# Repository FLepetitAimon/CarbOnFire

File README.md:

# Système CarbOnFire
***
## Contexte 
Le projet a été réalisé entre juin et aout 2021 au laboratoire d'aérologie de Toulouse, dans le cadre d'un stage de 4é année d'école d'ingénieur. La stage a été fait par François LEPETIT-AIMON et tutoré par Jean-François LEON. Si vous désirez des informations suplémentaires sur le projet, n'hésitez à contacter François LEPETIT-AIMON à l'adresse mail: francois.lepetitaimon@gmail.com

## Présentation du projet

ATTENTION : Avant d’utiliser le système, veillez à lire la fiche technique du projet.

CarbOnFire est un système de mesure d’émission de particules issues de la combustion de végétaux. Il s’inscrit dans un projet d’étude de l’exposition humaine aux particules fines issues de la combustion de biomasse et en particulier aux feux de forêt. Il est affilié au projet FIRECASTER de l’Agence National de la Recherche (ANR). Ce projet a pour but la création d'une plate-forme numérique de simulation des incendies de forêts et des panaches de fumée associées en zone méditerranéenne. Pour évaluer la quantité de fumée émise par un incendie, il est nécessaire de connaître les facteurs d'émission des polluants.  Les facteurs d’émission se définissent comme la masse d'un polluant spécifique émis dans l’atmosphère par kilogramme de végétation brûlée. Pour les évaluer, on mesure les rapports d'émission qui se définissent comme le rapport entre la masse de polluants émises sur celle des concentrations de CO et CO2. 

CarbOnFire est un système qui permet d’analyser la composition de fumées issues de combustions de végétaux. Le système est installé sur un sac à dos pour être facilement transportable.  Il est équipé d’un système de pompage qui aspire les fumées. L’aspiration se fait au bout d’un tuyau que l’utilisateur place au-dessus des feux. Le bout du tuyau est pourvu d’un filtre de quartz dont le rôle est de capter les particules. Après la mesure, le filtre est analysé au laboratoire par des méthodes chimiques, qui permettent de mettre en évidence sa composition. Les fumées filtrées qui arrivent du tuyau, circulent respectivement dans la pompe, le boîtier de mesure et enfin à travers le compteur à gaz. Elles sont ensuite rejetées dans l’air. Le cœur du système réside dans le boîtier de mesure. Il fait l’acquisition des concentrations de monoxyde (CO) et dioxyde de carbone (CO2), de la température et de la pression. Il enregistre les mesures dans une carte SD pour un traitement ultérieur, et transmet en direct, via Bluetooth, les mesures de gaz et de température. Celles-ci peuvent être visualisées sur le terrain avec un smartphone grâce à l’application CarbOnFire.

## Etat de fonctionnement du système

A l'issue des trois mois de développement, le premier prototype du système est en état de marche. Il fait l'acquisition des mesures de CO, CO2, température et pression. Il enregistre les données sur une carte SD et transmet les mesure de CO, CO2 et température vers une application android. L'ensemble du système est intégré sur un sac à dos. Les mesures réalisées en laboratoire et en conditions reélles ont permis de caractériser la qualité des mesures de gaz. Il en ressort qu la précision obtenue est insuffisante et qu'il faut l'améliorer. Le détail des mesures et de leur analyse est décrit dans la fiche technique du Projet.

## Contenu du Github

Le github contient les programmes arduino du projet, les documents techniques, le code de l'application android avec le fichier .apk, les fichiers des mesures réalisées, et enfin les fichiers associés à la conception du PCB.

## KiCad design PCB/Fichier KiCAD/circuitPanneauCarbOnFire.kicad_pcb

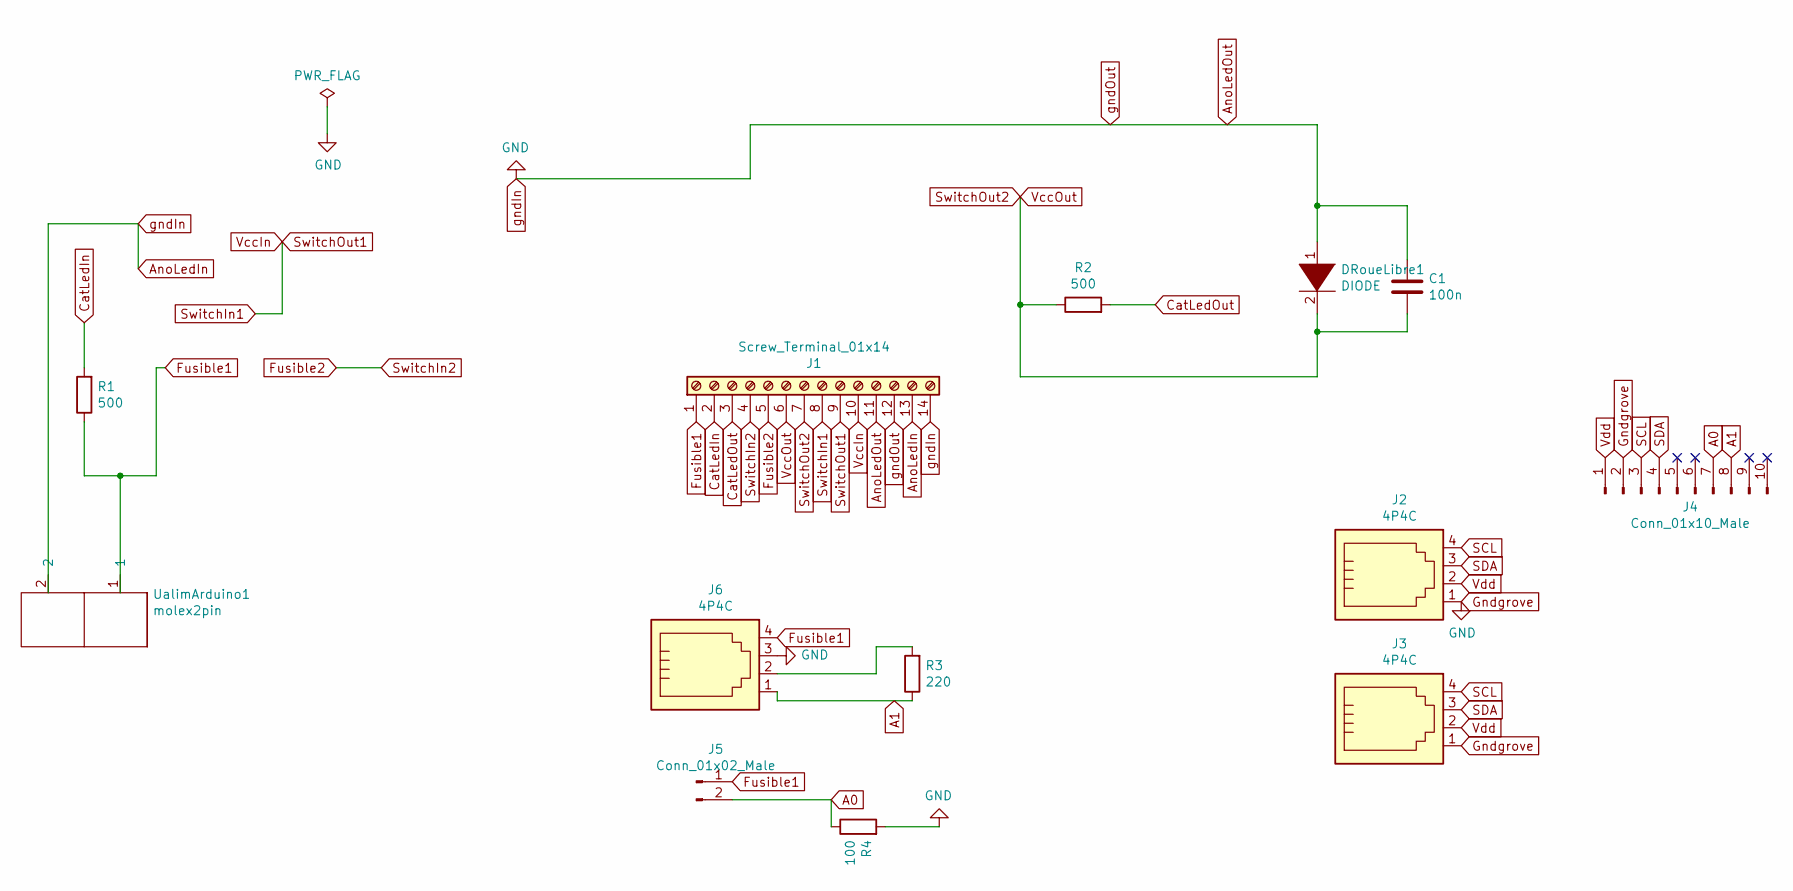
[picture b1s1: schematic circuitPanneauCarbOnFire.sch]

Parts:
C1: 100n; C_Rect_L9.0mm_W2.6mm_P7.50mm_MKT
DRoueLibre1: DIODE; D_A-405_P7.62mm_Horizontal
J1: Screw_Terminal_01x14; TerminalBlock_Phoenix_PT-1,5-14-5.0-H_1x14_P5.00mm_Horizont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
J2, J3: 4P4C; NS-Tech_Grove_1x04_P2mm_Vertical
J4: Conn_01x10_Male; PinSocket_1x10_P2.54mm_Vertical
J5: Conn_01x02_Male; Molex_KK-254_AE-6410-02A_1x02_P2.54mm_Vertical
J6: 4P4C; Molex_SL_171971-0004_1x04_P2.54mm_Vertical
R1, R2: 500; R_Axial_DIN0207_L6.3mm_D2.5mm_P10.16mm_Horizontal
R3: 220; R_Axial_DIN0207_L6.3mm_D2.5mm_P10.16mm_Horizontal
R4: 100; R_Axial_DIN0207_L6.3mm_D2.5mm_P10.16mm_Horizontal
UalimArduino1: molex2pin; Molex_KK-254_AE-6410-02A_1x02_P2.54mm_Vertical

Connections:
A0: J4.7, J5.2, R4.1
A1: J4.8, J6.1, R3.1
AnoLedIn: C1.2, DRoueLibre1.1 (K), J1.11, J1.12, J1.13, J1.14, J2.1, J3.1, J4.2, J6.3, R4.2, UalimArduino1.2
CatLedIn: J1.2, R1.2
CatLedOut: J1.3, R2.2
Fusible1: J1.1, J5.1, J6.4, R1.1, UalimArduino1.1
Fusible2: J1.4, J1.5
unnamed: J6.2, R3.2
SCL: J2.4, J3.4, J4.3
SDA: J2.3, J3.3, J4.4
SwitchIn1: J1.8, J1.9, J1.10
SwitchOut2: C1.1, DRoueLibre1.2 (A), J1.6, J1.7, R2.1
Vdd: J2.2, J3.2, J4.1

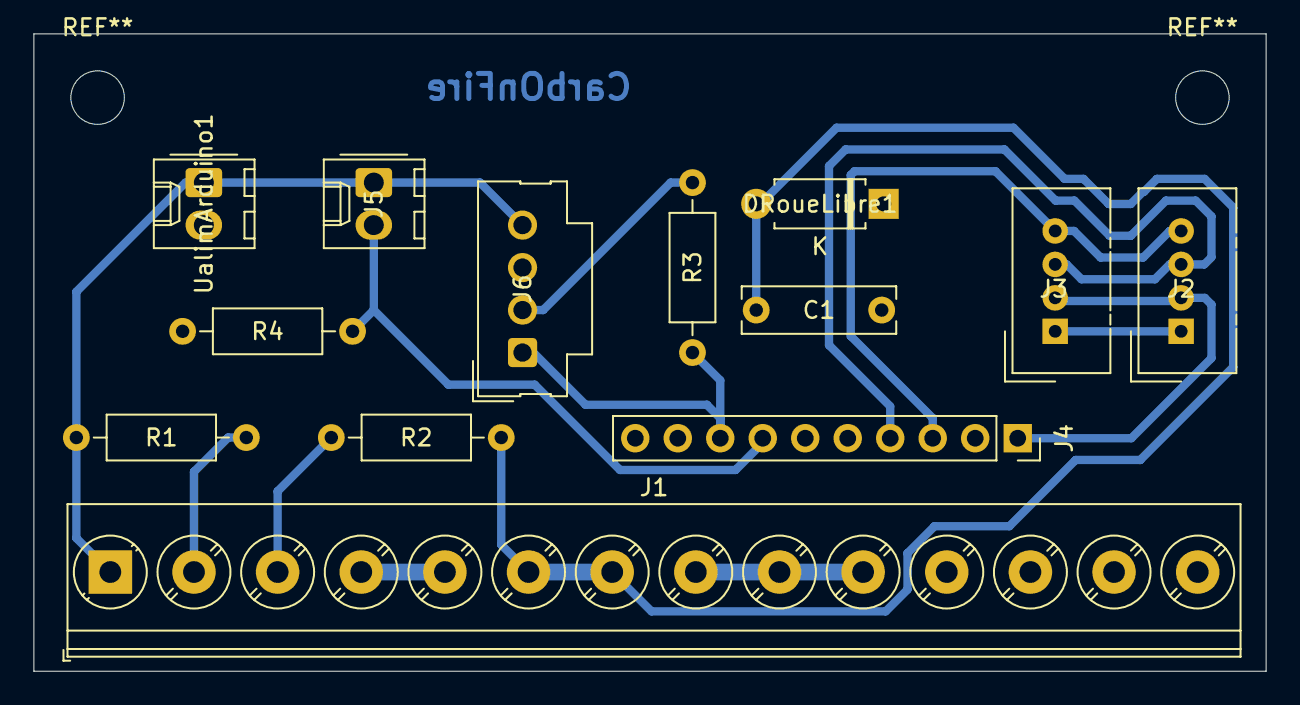
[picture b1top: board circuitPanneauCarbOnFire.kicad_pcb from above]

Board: 2 copper layers, 73.7 x 38.1 mm, 13 parts (0 on the bottom side), 13 nets.

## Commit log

2021-06-25 initialisation du repertoire
2021-07-06 init
2021-07-06 init application
2021-07-06 test pull
2021-07-06 fichier gerber
2021-07-08 circuit electrique grove+capteur+panneauAvant
2021-07-09 KiCAD nettoyage dossier librairie
2021-07-12 fichier csv + getCurrentMeasurement
2021-07-12 Application Layout activity main - V2.0
2021-07-13 application V1.1
2021-07-15 Application V1.2
2021-07-16 init programme analog instrument
2021-07-16 ajout de fonction d'acquisition de mesure
2021-07-19 Application V1.0.1
2021-07-19 vérification avant impression
2021-07-19 renommage de dossier + ajout fiche technique
2021-07-20 pin analog read
2021-07-20 avancement rapport V0.1
2021-07-22 ajout data étallonage + avancement fiche technique
2021-07-22 init courbe des résultats
2021-07-22 avancement fiche technique
2021-07-27 script python + pcb
2021-07-27 pcb + script python
2021-07-27 pcb+script python
2021-07-28 nettoyage programme principale
2021-07-28 init analyse des résultats 22/07/21
2021-07-28 ajout de commentaire
2021-07-28 avancement fiche technique programme arduino
2021-08-04 init gestion de projet
2021-08-04 début partie application
2021-08-05 journal de bord 05/08
2021-08-05 rédaction rapport application suite
2021-08-05 appplication V1.1
2021-08-08 avacnement fiche tecnhique
2021-08-09 journal 09/08
2021-08-11 10/08
2021-08-11 11/08
2021-08-12 12/08
2021-08-13 13/09
2021-08-16 compraison 0ppm cart analog VS alphasense
2021-08-16 courbe CN-CX + impact debit
2021-08-17 17/08
2021-08-17 changement de repertoire python
2021-08-17 avacnement fiche technique
2021-08-18 18/08
2021-08-19 relecture jusqu'à "panneau face avant"
2021-08-19 relecture jusqu'à instruction d'utilisation
2021-08-23 23/08
2021-08-24 24/08
2021-08-25 25/08
2021-08-26 26/08
2021-08-26 voie 0 - CO
2021-08-27 renmmage des dossier
2021-08-27 mesure 17-08
2021-08-31 mesure 31/08
2021-09-02 02/09
2021-09-06 Rename README to README.md
2021-09-09 ajout de commentaires
2022-06-20 comit
